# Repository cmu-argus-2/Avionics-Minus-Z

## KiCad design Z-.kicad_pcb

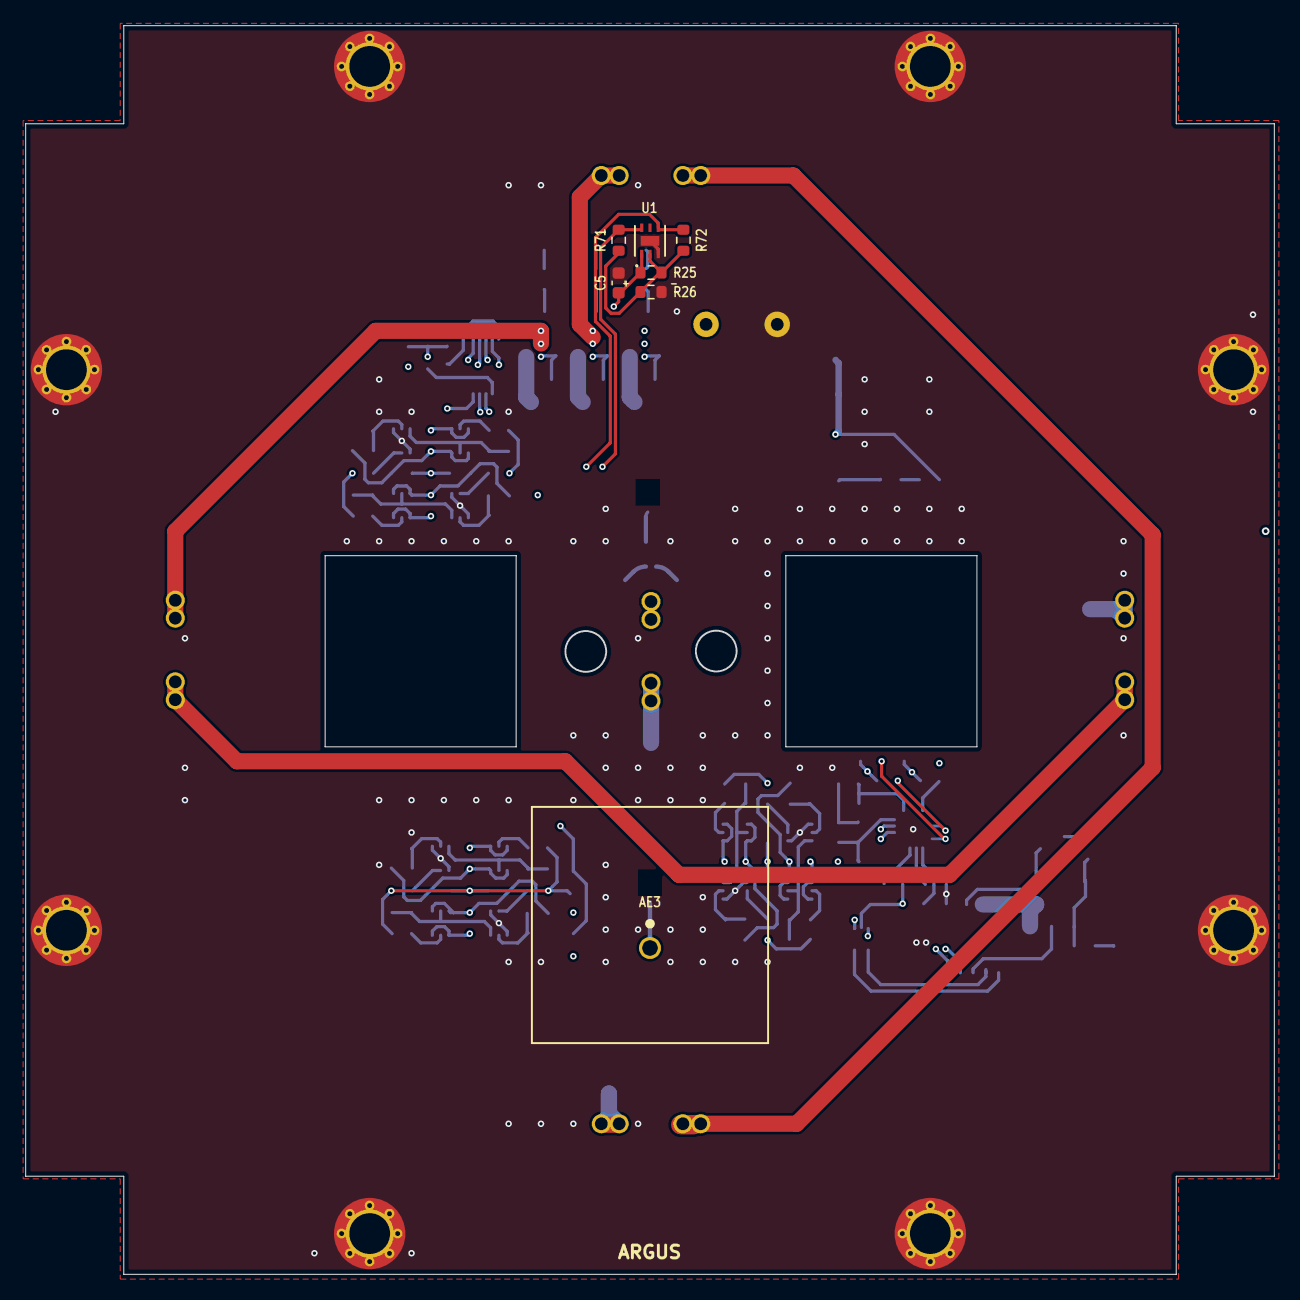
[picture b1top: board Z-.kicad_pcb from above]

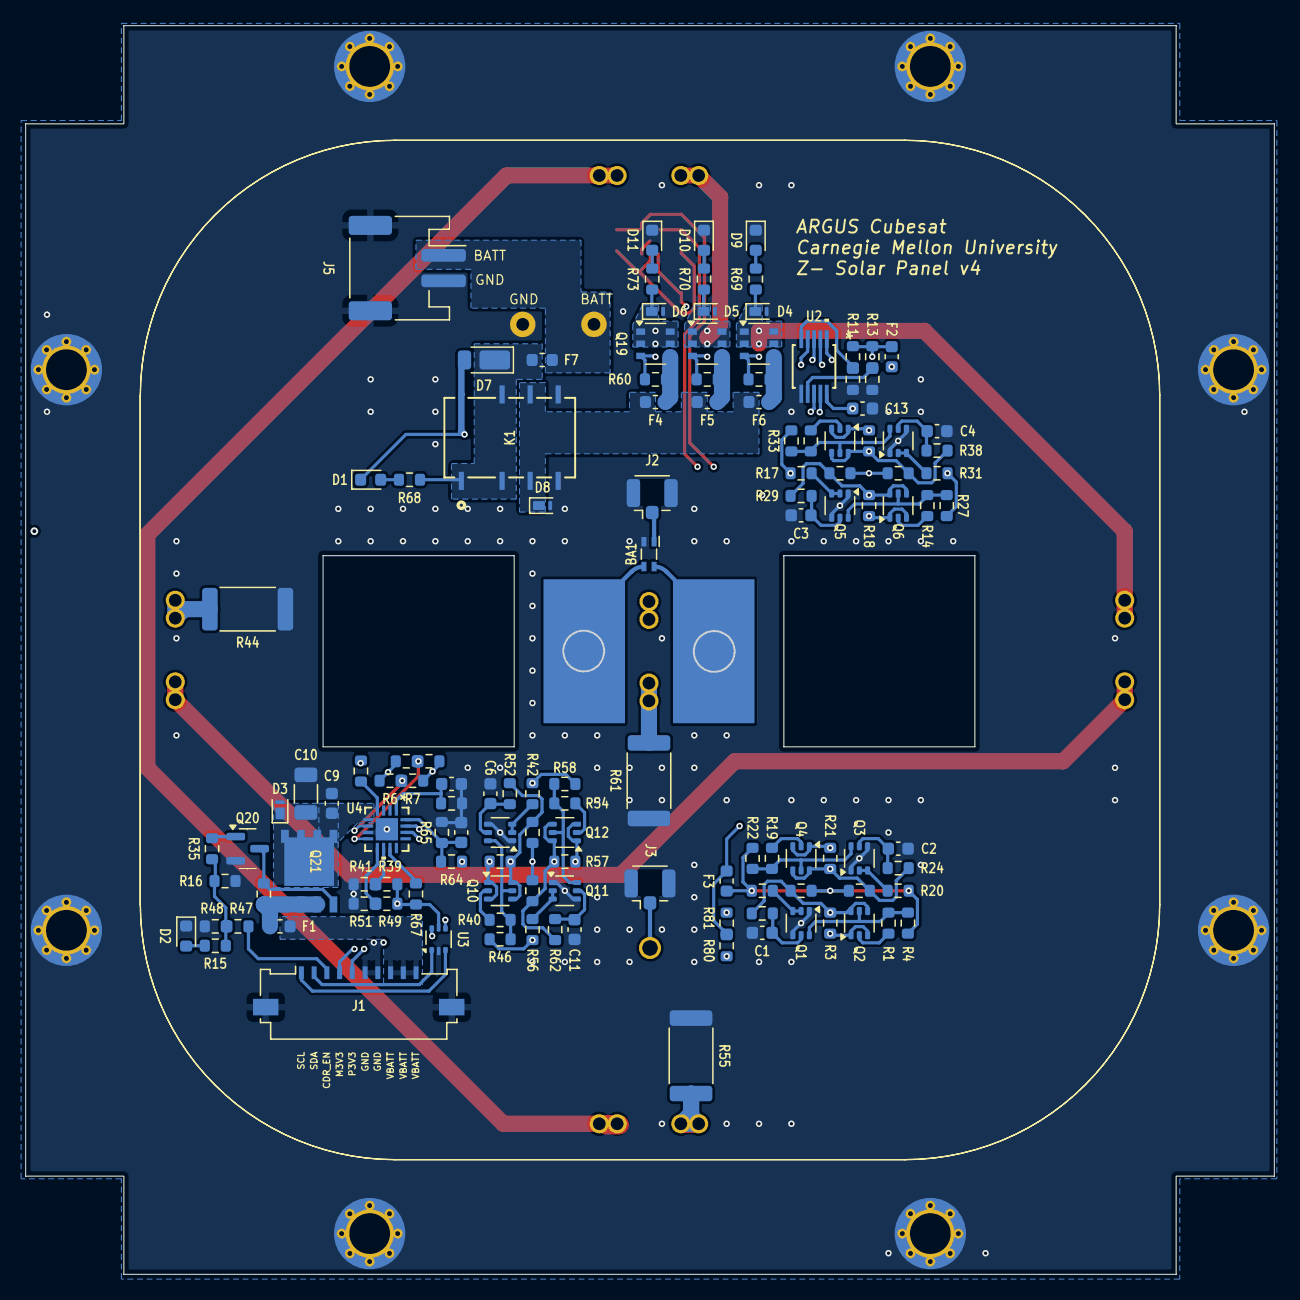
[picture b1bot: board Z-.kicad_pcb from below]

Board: 4 copper layers, 98.0 x 98.0 mm, 150 parts (130 on the bottom side), 86 nets.

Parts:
AE1, AE2: MountingHole_Pad; Antenna Mount v2
AE3: CGGBP.18.4.A.02; ANT_CGGBP.18.4.A.02_TAL
BA1: DXW21HN5011BL; ATB2012
C1, C2, C3, C4, C6, C11: 10nF; C_0603_1608Metric
C5, C7, C9, C13: 0.1uF; C_0603_1608Metric
C8: 1nF; C_0603_1608Metric
C10: 10uF; C_1206_3216Metric
D1, D2, D9, D10, D11: GREEN; LED_0603_1608Metric
D3, D4, D5, D6, D8: 10V; Nexperia_DSN1608-2_1.6x0.8mm
D7: DFLS130L; D_PowerDI-123
F1, F2, F3: 500mA; Fuse_0603_1608Metric
F4, F5, F6: 2A; Fuse_0603_1608Metric
F7: 5A; Fuse_0603_1608Metric
H1, H2, H3, H4, H5, H6, H7, H8: MountingHole_Pad; MountingHole_3.2mm_M3_DIN965_Pad_TopBottom
H9, H10: MountingHole_Pad; 20AWG Through Hole
J1: 200528-0100; Molex_200528-0100_1x10-1MP_P1.00mm_Horizontal
J2, J3: U.FL; U.FL_Hirose_U.FL-R-SMT-1_Vertical
J5: Conn_01x02; JST_PH_S2B-PH-SM4-TB_1x02-1MP_P2.00mm_Horizontal
JP1, JP2, JP3, JP4, JP5: BurnWire; Burn-Wire
K1: IM02; RELAY8_SMTGUL_TEC
Q1, Q3, Q5, Q7, Q9, Q11: NX3008NBKS; SOT-363_SC-70-6
Q2, Q4, Q6, Q8, Q10, Q12: MBT2222ADW1T1; SOT-363_SC-70-6
Q15, Q17, Q19: IRFTS9342PBF; TSOP-6_1.65x3.05mm_P0.95mm
Q20: IRLML2803; SOT-23
Q21: SiRA99DP; PowerPAK SO-8
R1, R14, R19, R30, R40, R54: 680R; R_0603_1608Metric
R2, R17, R20, R31, R42, R56: 100K; R_0603_1608Metric
R3, R18, R21, R32, R45, R57: DNI (0R); R_0603_1608Metric
R4, R5, R22, R23, R27, R28, R33, R34, R46, R50, R58, R59: 10K; R_0603_1608Metric
R6, R7, R8, R9, R11, R12, R13, R25, R26, R37, R39, R41, R47, R48, R49, R51, R67, R71, R72, R80, R81: 0R; R_0603_1608Metric
R10, R24, R29, R38, R52, R62: 200K; R_0603_1608Metric
R15, R68, R69, R70, R73: 2.7k; R_0603_1608Metric
R16, R36, R63: 10k; R_0603_1608Metric
R35: 4k7; R_0603_1608Metric
R43, R53, R60: 1k; R_0603_1608Metric
R44, R55, R61: 1R; R_2512_6332Metric
R64, R65: TBD; R_0603_1608Metric
R66: 560R; R_0603_1608Metric
U1: OPT4003DNPRQ1; OPT4003
U2: PCA9633DP2; SOT552-1_NXP
U3: USBLC6-2P6; SOT-666
U4: DRV8235RTER; WQFN16_RTE_TEX

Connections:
/Burn Wires/VBURN1: D4.1 (K), JP1.1 (A), Q15.1 (D), Q15.2 (D), Q15.5 (D), Q15.6 (D), R69.1
/Burn Wires/VBURN2: D5.1 (K), JP2.1 (A), Q17.1 (D), Q17.2 (D), Q17.5 (D), Q17.6 (D), R70.1
/Burn Wires/VBURN3: D6.1 (K), JP3.1 (A), Q19.1 (D), Q19.2 (D), Q19.5 (D), Q19.6 (D), R73.1
/Burn Wires/VBURN_A_IN: D8.1 (K), F4.2, F5.2, F6.2, K1.3, K1.6
/COIL_DRIVER_EN_OR_MAIN_3V3: J1.3, R47.1
/GPS: AE3.1 (A), J3.1 (In)
/I2C Devices/A0_COIL: R39.1, R41.2, U4.10 (A0)
/I2C Devices/A0_IO: R11.1, R12.2, U2.5 (A0)
/I2C Devices/A1_COIL: R49.1, R51.2, U4.9 (A1)
/I2C Devices/A1_IO: R13.1, R37.2, U2.7 (A1)
/I2C Devices/ADDR: R25.1, R26.2, R71.1, R72.2, U1.2 (ADDR)
/I2C Devices/IPROPI: C8.1, R66.1, U4.1 (IPROPI)
/I2C Devices/VM: C9.1, C10.1, D3.1 (K), Q21.2 (D), U4.5 (VM)
/I2C Devices/VREF: C7.1, R64.2, R65.1, U4.16 (VREF)
/PERI_3V3_OR_GND: J1.5, R80.1
/coil: R6.2, R7.1, R8.2, R9.1
BURN_EN1: Q15.3 (G), R43.1, U2.1 (LED0)
BURN_EN2: Q17.3 (G), R53.1, U2.2 (LED1)
BURN_EN3: Q19.3 (G), R60.1, U2.3 (LED2)
BURN_RELAY_A: D1.1 (K), D7.2 (A), K1.8, U2.4 (LED3)
BW_3V3: C13.1, F2.1, R17.1, R27.1, R28.1, R31.1, R33.1, R34.1, U2.10 (VDD)
COIL_DRIVER_EN: R15.1, R16.2, R35.1, R47.2, R48.2
COIL_N: R8.1, R9.2, U4.8 (OUT2)
COIL_P: R6.1, R7.2, U4.6 (OUT1)
GND: BA1.2 (GND), C1.2, C2.2, C3.2, C4.2, C5.2, C6.2, C7.2, C8.2, C9.2, C10.2, C11.2, C13.2, D2.1 (K), D3.2 (A), D4.2 (A), D5.2 (A), D6.2 (A), D8.2 (A), D9.1 (K), D10.1 (K), D11.1 (K), H1.1, H2.1, H3.1, H4.1, H5.1, H6.1, H7.1, H8.1, H10.1, J1.6, J1.7, J1.MP (MountPin), J2.2 (Ext), J3.2 (Ext), J5.2, J5.MP (MountPin), K1.4, K1.5, Q1.1 (S2), Q1.4 (S1), Q3.1 (S2), Q3.4 (S1), Q5.1 (S2), Q5.4 (S1), Q7.1 (S2), Q7.4 (S1), Q9.1 (S2), Q9.4 (S1), Q11.1 (S2), Q11.4 (S1), Q20.2 (S), R12.1, R16.1, R26.1, R37.1, R41.1, R44.1, R48.1, R51.1, R55.1, R61.1, R65.2, R66.2, U1.3 (GND), U1.7 (EPAD), U2.6 (VSS), U3.2 (GND), U4.7 (GND), U4.17 (EPAD)
LS_3V3: C5.1, F3.1, R2.1, R4.1, R5.1, R20.1, R22.1, R23.1, R25.2, U1.1 (VDD)
MAIN_3V3: J1.4, R39.2, R42.1, R46.1, R49.2, R50.1, R56.1, R58.1, R59.1, R63.1, R64.1, R67.2, R81.1, U3.5 (VBUS)
unnamed: AE1.1, BA1.3
unnamed: AE2.1, BA1.4
unnamed: D1.2 (A), R68.2
unnamed: D2.2 (A), R15.2
unnamed: D7.1 (K), F7.1, K1.1, K1.2, K1.7, R68.1
unnamed: D9.2 (A), R69.2
unnamed: D10.2 (A), R70.2
unnamed: D11.2 (A), R73.2
unnamed: J1.1, U3.3 (I/O2)
unnamed: J1.2, U3.1 (I/O1)
unnamed: BA1.1, J2.1 (In)
unnamed: JP1.2 (B), JP4.1 (A)
unnamed: JP2.2 (B), JP5.1 (A)
unnamed: JP3.2 (B), R61.2
unnamed: JP4.2 (B), R44.2
unnamed: JP5.2 (B), R55.2
unnamed: Q1.6 (D1), Q2.5 (B2), R1.2, R4.2
unnamed: Q1.2 (G2), Q1.3 (D2), R2.2
unnamed: C1.1, Q1.5 (G1), R10.2
unnamed: Q2.2 (B1), R1.1
unnamed: Q3.6 (D1), Q4.5 (B2), R19.2, R22.2
unnamed: Q3.2 (G2), Q3.3 (D2), R20.2
unnamed: C2.1, Q3.5 (G1), R24.2
unnamed: Q4.2 (B1), R19.1
unnamed: Q5.6 (D1), Q6.5 (B2), R14.2, R27.2
unnamed: Q5.2 (G2), Q5.3 (D2), R17.2
unnamed: C3.1, Q5.5 (G1), R29.2
unnamed: Q6.2 (B1), R14.1
unnamed: Q7.6 (D1), Q8.5 (B2), R30.2, R33.2
unnamed: Q7.2 (G2), Q7.3 (D2), R31.2
unnamed: C4.1, Q7.5 (G1), R38.2
unnamed: Q8.2 (B1), R30.1
unnamed: Q9.2 (G2), Q9.3 (D2), R42.2
unnamed: C6.1, Q9.5 (G1), R52.2
unnamed: Q10.2 (B1), R40.1
unnamed: Q9.6 (D1), Q10.5 (B2), R40.2, R46.2
unnamed: Q11.6 (D1), Q12.5 (B2), R54.2, R58.2
unnamed: Q11.2 (G2), Q11.3 (D2), R56.2
unnamed: C11.1, Q11.5 (G1), R62.2
unnamed: Q12.2 (B1), R54.1
unnamed: F6.1, Q15.4 (S), R43.2
unnamed: F5.1, Q17.4 (S), R53.2
unnamed: F4.1, Q19.4 (S), R60.2
unnamed: Q20.3 (D), Q21.1 (G), R36.1
unnamed: Q20.1 (G), R35.2
unnamed: F1.1, Q21.3 (S), R36.2
unnamed: R63.2, U4.4 (NFAULT)
unnamed: R67.1, U4.11 (NSLEEP)
PERI_3V3: F2.2, F3.2, R11.2, R13.2, R80.2, R81.2
SCL: Q4.1 (E1), Q4.3 (C2), Q6.1 (E1), Q6.3 (C2), Q10.1 (E1), Q10.3 (C2), R18.2, R21.2, R45.2, U3.4 (I/O2)
SCL_IO: Q6.4 (E2), Q6.6 (C1), R18.1, R28.2, R29.1, U2.8 (SCL)
SCL_LS: Q4.4 (E2), Q4.6 (C1), R21.1, R23.2, R24.1, R72.1, U1.4 (SCL)
SCL_M: Q10.4 (E2), Q10.6 (C1), R45.1, R50.2, R52.1, U4.15 (SCL)
SDA: Q2.1 (E1), Q2.3 (C2), Q8.1 (E1), Q8.3 (C2), Q12.1 (E1), Q12.3 (C2), R3.2, R32.2, R57.2, U3.6 (I/O1)
SDA_IO: Q8.4 (E2), Q8.6 (C1), R32.1, R34.2, R38.1, U2.9 (SDA)
SDA_LS: Q2.4 (E2), Q2.6 (C1), R3.1, R5.2, R10.1, R71.2, U1.6 (SDA)
SDA_M: Q12.4 (E2), Q12.6 (C1), R57.1, R59.2, R62.1, U4.14 (SDA)
VBATT: F7.2, H9.1, J5.1
VBATT_SENSE: F1.2, J1.8, J1.9, J1.10

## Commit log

2025-02-04 Updated filepaths
2025-02-13 Added more silkscreen, switched to PMOS instead of mech relay
2025-02-17 Added minus-z BOM
2025-02-18 Updated burnwire footprint and fuse specs
2025-02-28 Started adding pmos -> relay
2025-02-28 Updated git ignore
2025-02-28 Minor layout tweaks and gerbers exported
2025-03-01 Renamed gerber files
2025-03-07 Added temp step export
2025-03-13 push
2025-03-13 updated relay with old relay
2025-03-13 Updated PCB
2025-03-14 Done, still needs silkscreen
2025-03-14 Updated silkscreen and gps/antenna parameters for 50ohm
2025-03-26 Updated burnwire circuitry and layout
2025-06-24 Stash
2025-11-18 Stash 2
2025-11-19 resistor values
2026-01-21 Update DNP list
2026-02-09 V6 Updates
2026-03-23 Coil direction comment clarification
